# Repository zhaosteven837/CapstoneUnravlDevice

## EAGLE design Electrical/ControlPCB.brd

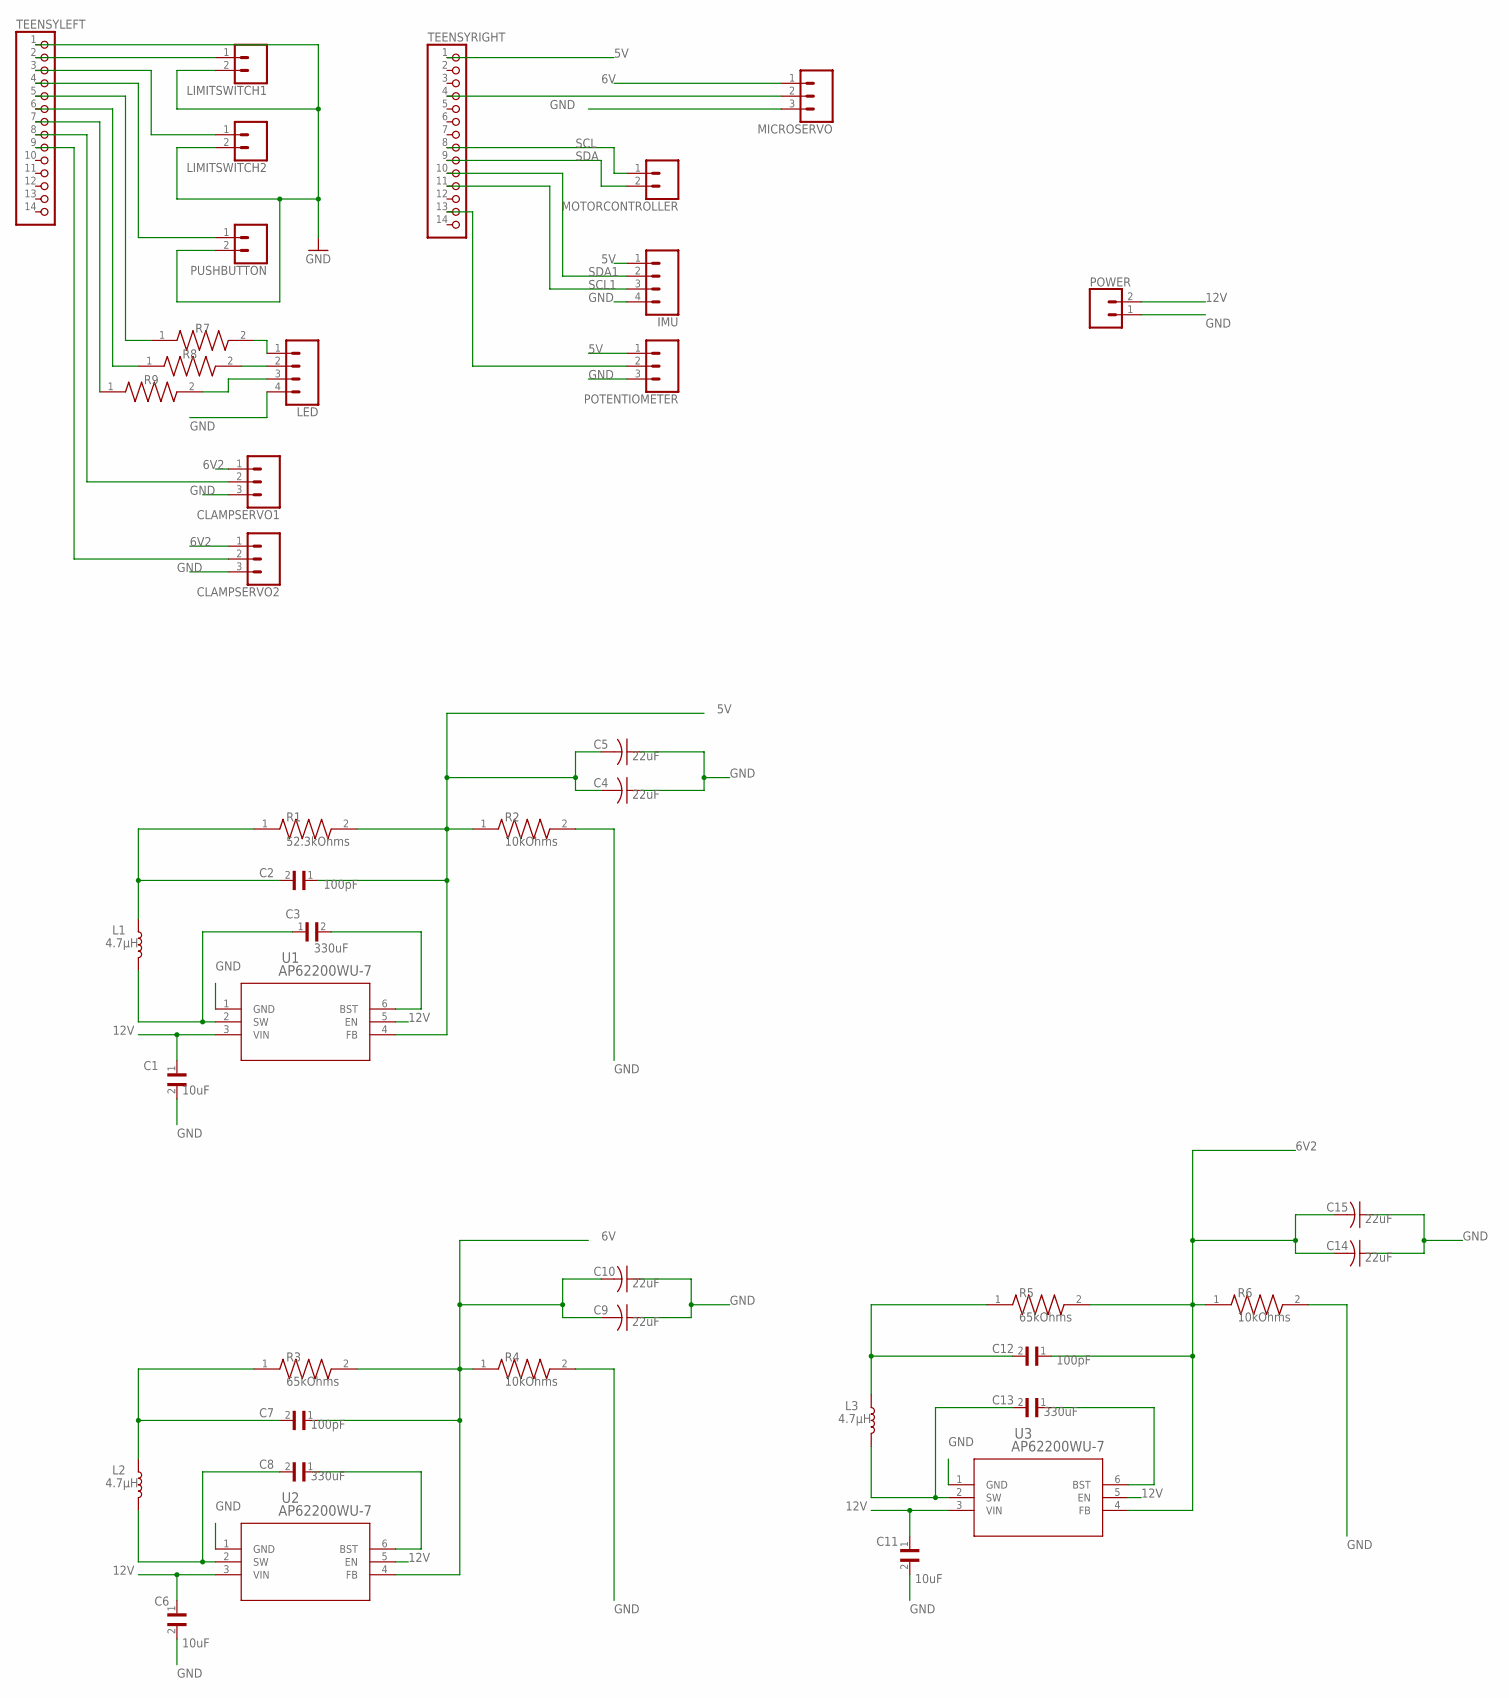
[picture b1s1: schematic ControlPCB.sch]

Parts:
C1, C6, C11: 10uF; CAPC1608X90N
C2, C7, C12: 100pF; CAPC0603X33N
C3, C8, C13: 330uF; CAPC3225X280N
C4, C5, C9, C10, C14, C15: 22uF; C0402
CLAMPSERVO1, CLAMPSERVO2: CONN_03SCREW; SCREWTERMINAL-3.5MM-3
IMU: CONN_04SCREW; SCREWTERMINAL-3.5MM-4
L1, L2, L3: 4.7μH; INDUCTOR_4X4MM
LED: CONN_04SCREW; SCREWTERMINAL-3.5MM-4
LIMITSWITCH1, LIMITSWITCH2: CONN_023.5MM; SCREWTERMINAL-3.5MM-2
MICROSERVO: CONN_03SCREW; SCREWTERMINAL-3.5MM-3
MOTORCONTROLLER: CONN_023.5MM; SCREWTERMINAL-3.5MM-2
POTENTIOMETER: CONN_03SCREW; SCREWTERMINAL-3.5MM-3
POWER: CONN_023.5MM; SCREWTERMINAL-3.5MM-2
PUSHBUTTON: CONN_023.5MM; SCREWTERMINAL-3.5MM-2
R1: 52.3kOhms; RES_ERJ1GNF1000C
R2, R4, R6: 10kOhms; RES_ERJ1GNF1000C
R3, R5: 65kOhms; RES_ERJ1GNF1000C
R7, R8, R9: 100Ohm; RES_ERJ1GNF1000C
TEENSYLEFT: PINHD-1X14; 1X14
TEENSYRIGHT: PINHD-1X14; 1X14
U1, U2, U3: AP62200WU-7; TSOT26-WU_DIO

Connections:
5V: C2.1, C4.2, C5.2, IMU.1, POTENTIOMETER.1, R1.2, R2.1, TEENSYRIGHT.1, U1.4 (FB)
6V: C7.1, C9.2, C10.2, MICROSERVO.1, R3.2, R4.1, U2.4 (FB)
6V2: C12.1, C14.2, C15.2, CLAMPSERVO1.1, CLAMPSERVO2.1, R5.2, R6.1, U3.4 (FB)
12V: C1.1, C6.1, C11.1, POWER.2, U1.3 (VIN), U1.5 (EN), U2.3 (VIN), U2.5 (EN), U3.3 (VIN), U3.5 (EN)
GND: C1.2, C4.1, C5.1, C6.2, C9.1, C10.1, C11.2, C14.1, C15.1, CLAMPSERVO1.3, CLAMPSERVO2.3, IMU.4, LED.4, LIMITSWITCH1.2, LIMITSWITCH2.2, MICROSERVO.3, POTENTIOMETER.3, POWER.1, PUSHBUTTON.2, R2.2, R4.2, R6.2, TEENSYLEFT.1, U1.1 (GND), U2.1 (GND), U3.1 (GND)
unnamed: LIMITSWITCH1.1, TEENSYLEFT.2
unnamed: LIMITSWITCH2.1, TEENSYLEFT.3
unnamed: PUSHBUTTON.1, TEENSYLEFT.4
unnamed: MICROSERVO.2, TEENSYRIGHT.4
unnamed: R7.1, TEENSYLEFT.5
unnamed: R8.1, TEENSYLEFT.6
unnamed: R9.1, TEENSYLEFT.7
unnamed: CLAMPSERVO1.2, TEENSYLEFT.8
unnamed: C2.2, L1.P$1 (1), R1.1
unnamed: C3.1, L1.P$2 (2), U1.2 (SW)
unnamed: CLAMPSERVO2.2, TEENSYLEFT.9
unnamed: C3.2, U1.6 (BST)
unnamed: C7.2, L2.P$1 (1), R3.1
unnamed: C8.2, L2.P$2 (2), U2.2 (SW)
unnamed: POTENTIOMETER.2, TEENSYRIGHT.13
unnamed: C8.1, U2.6 (BST)
unnamed: C12.2, L3.P$1 (1), R5.1
unnamed: C13.2, L3.P$2 (2), U3.2 (SW)
unnamed: LED.1, R7.2
unnamed: LED.2, R8.2
unnamed: LED.3, R9.2
unnamed: C13.1, U3.6 (BST)
SCL: MOTORCONTROLLER.1, TEENSYRIGHT.8
SCL1: IMU.3, TEENSYRIGHT.11
SDA: MOTORCONTROLLER.2, TEENSYRIGHT.9
SDA1: IMU.2, TEENSYRIGHT.10

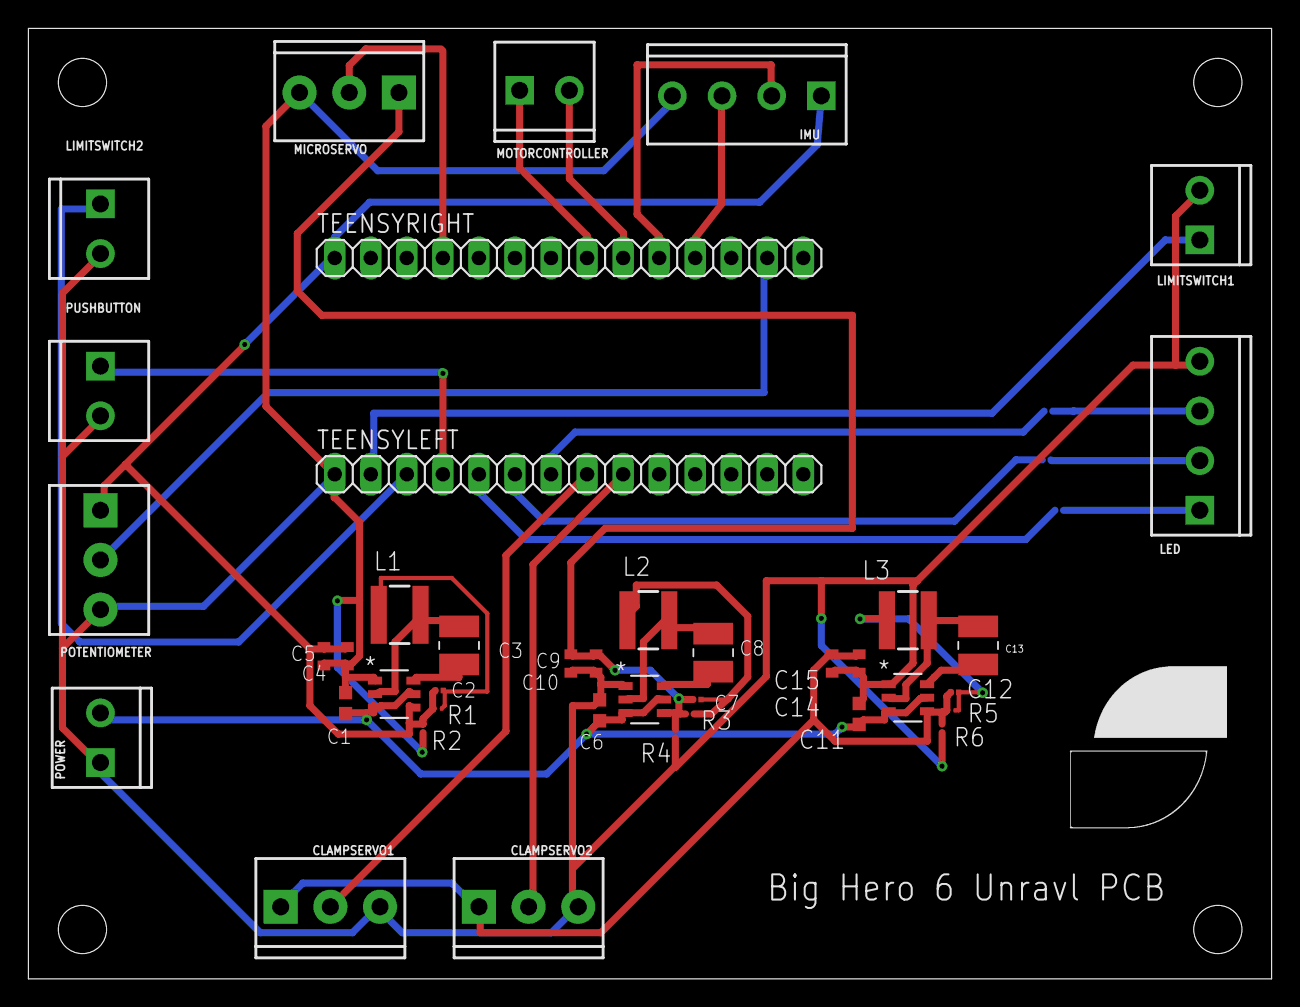
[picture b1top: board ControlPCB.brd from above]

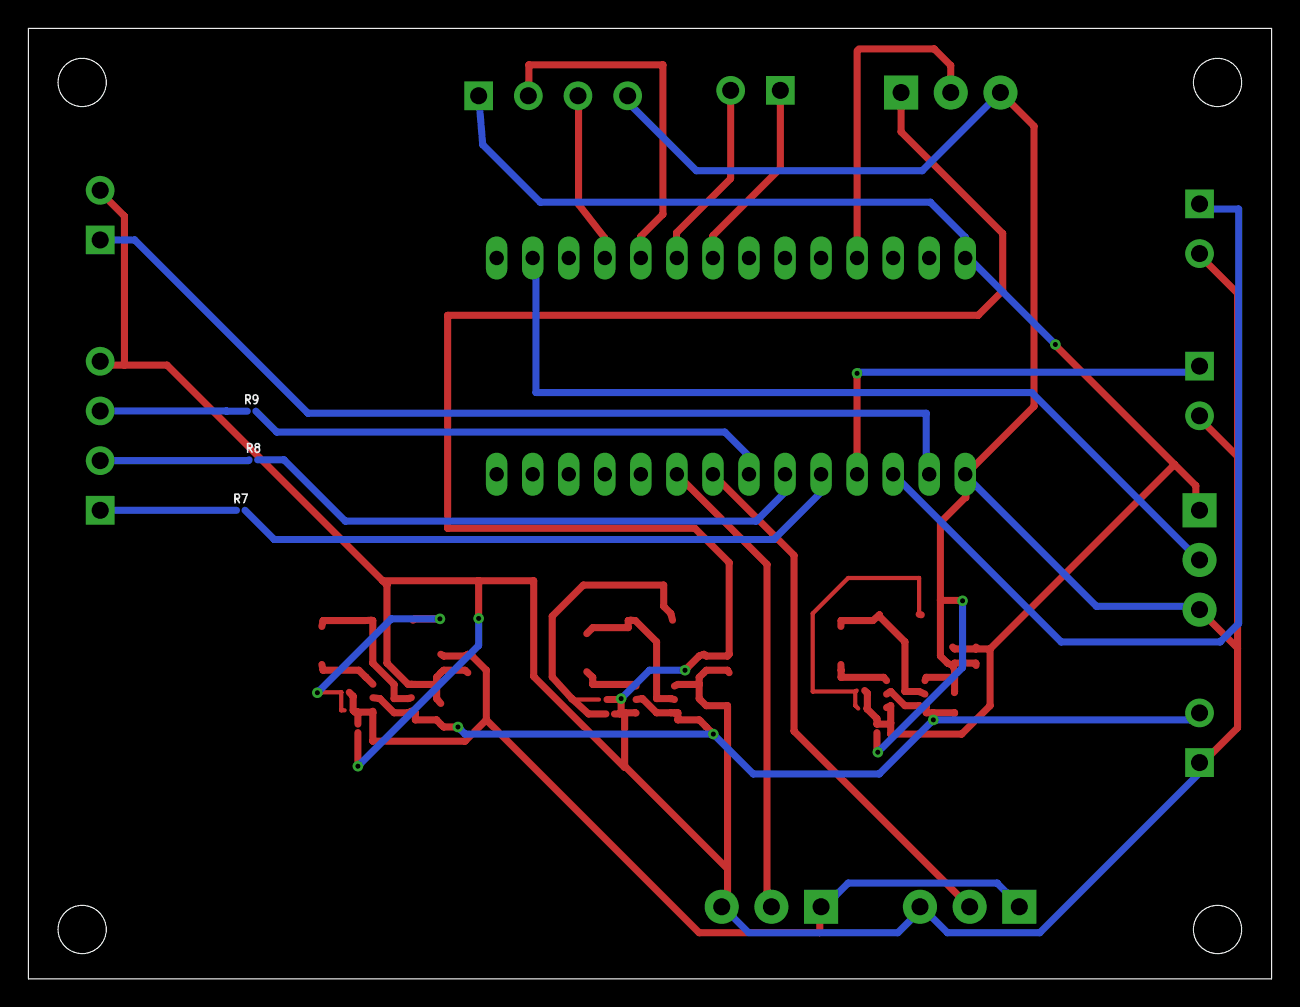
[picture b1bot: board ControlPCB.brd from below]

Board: 2 copper layers, 87.6 x 67.0 mm, 43 parts (3 on the bottom side), 31 nets.

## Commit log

2023-11-15 Adding PlatformIO framework
2023-12-04 Adding main code

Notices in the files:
parts and their libraries:
SparkFun-Connectors: Licensing: Creative Commons ShareAlike 4.0 International - https://creativecommons.org/licenses/by-sa/4.0
COPYRIGHT: Copyright (C) 2023 Ultra Librarian. All rights reserved.
